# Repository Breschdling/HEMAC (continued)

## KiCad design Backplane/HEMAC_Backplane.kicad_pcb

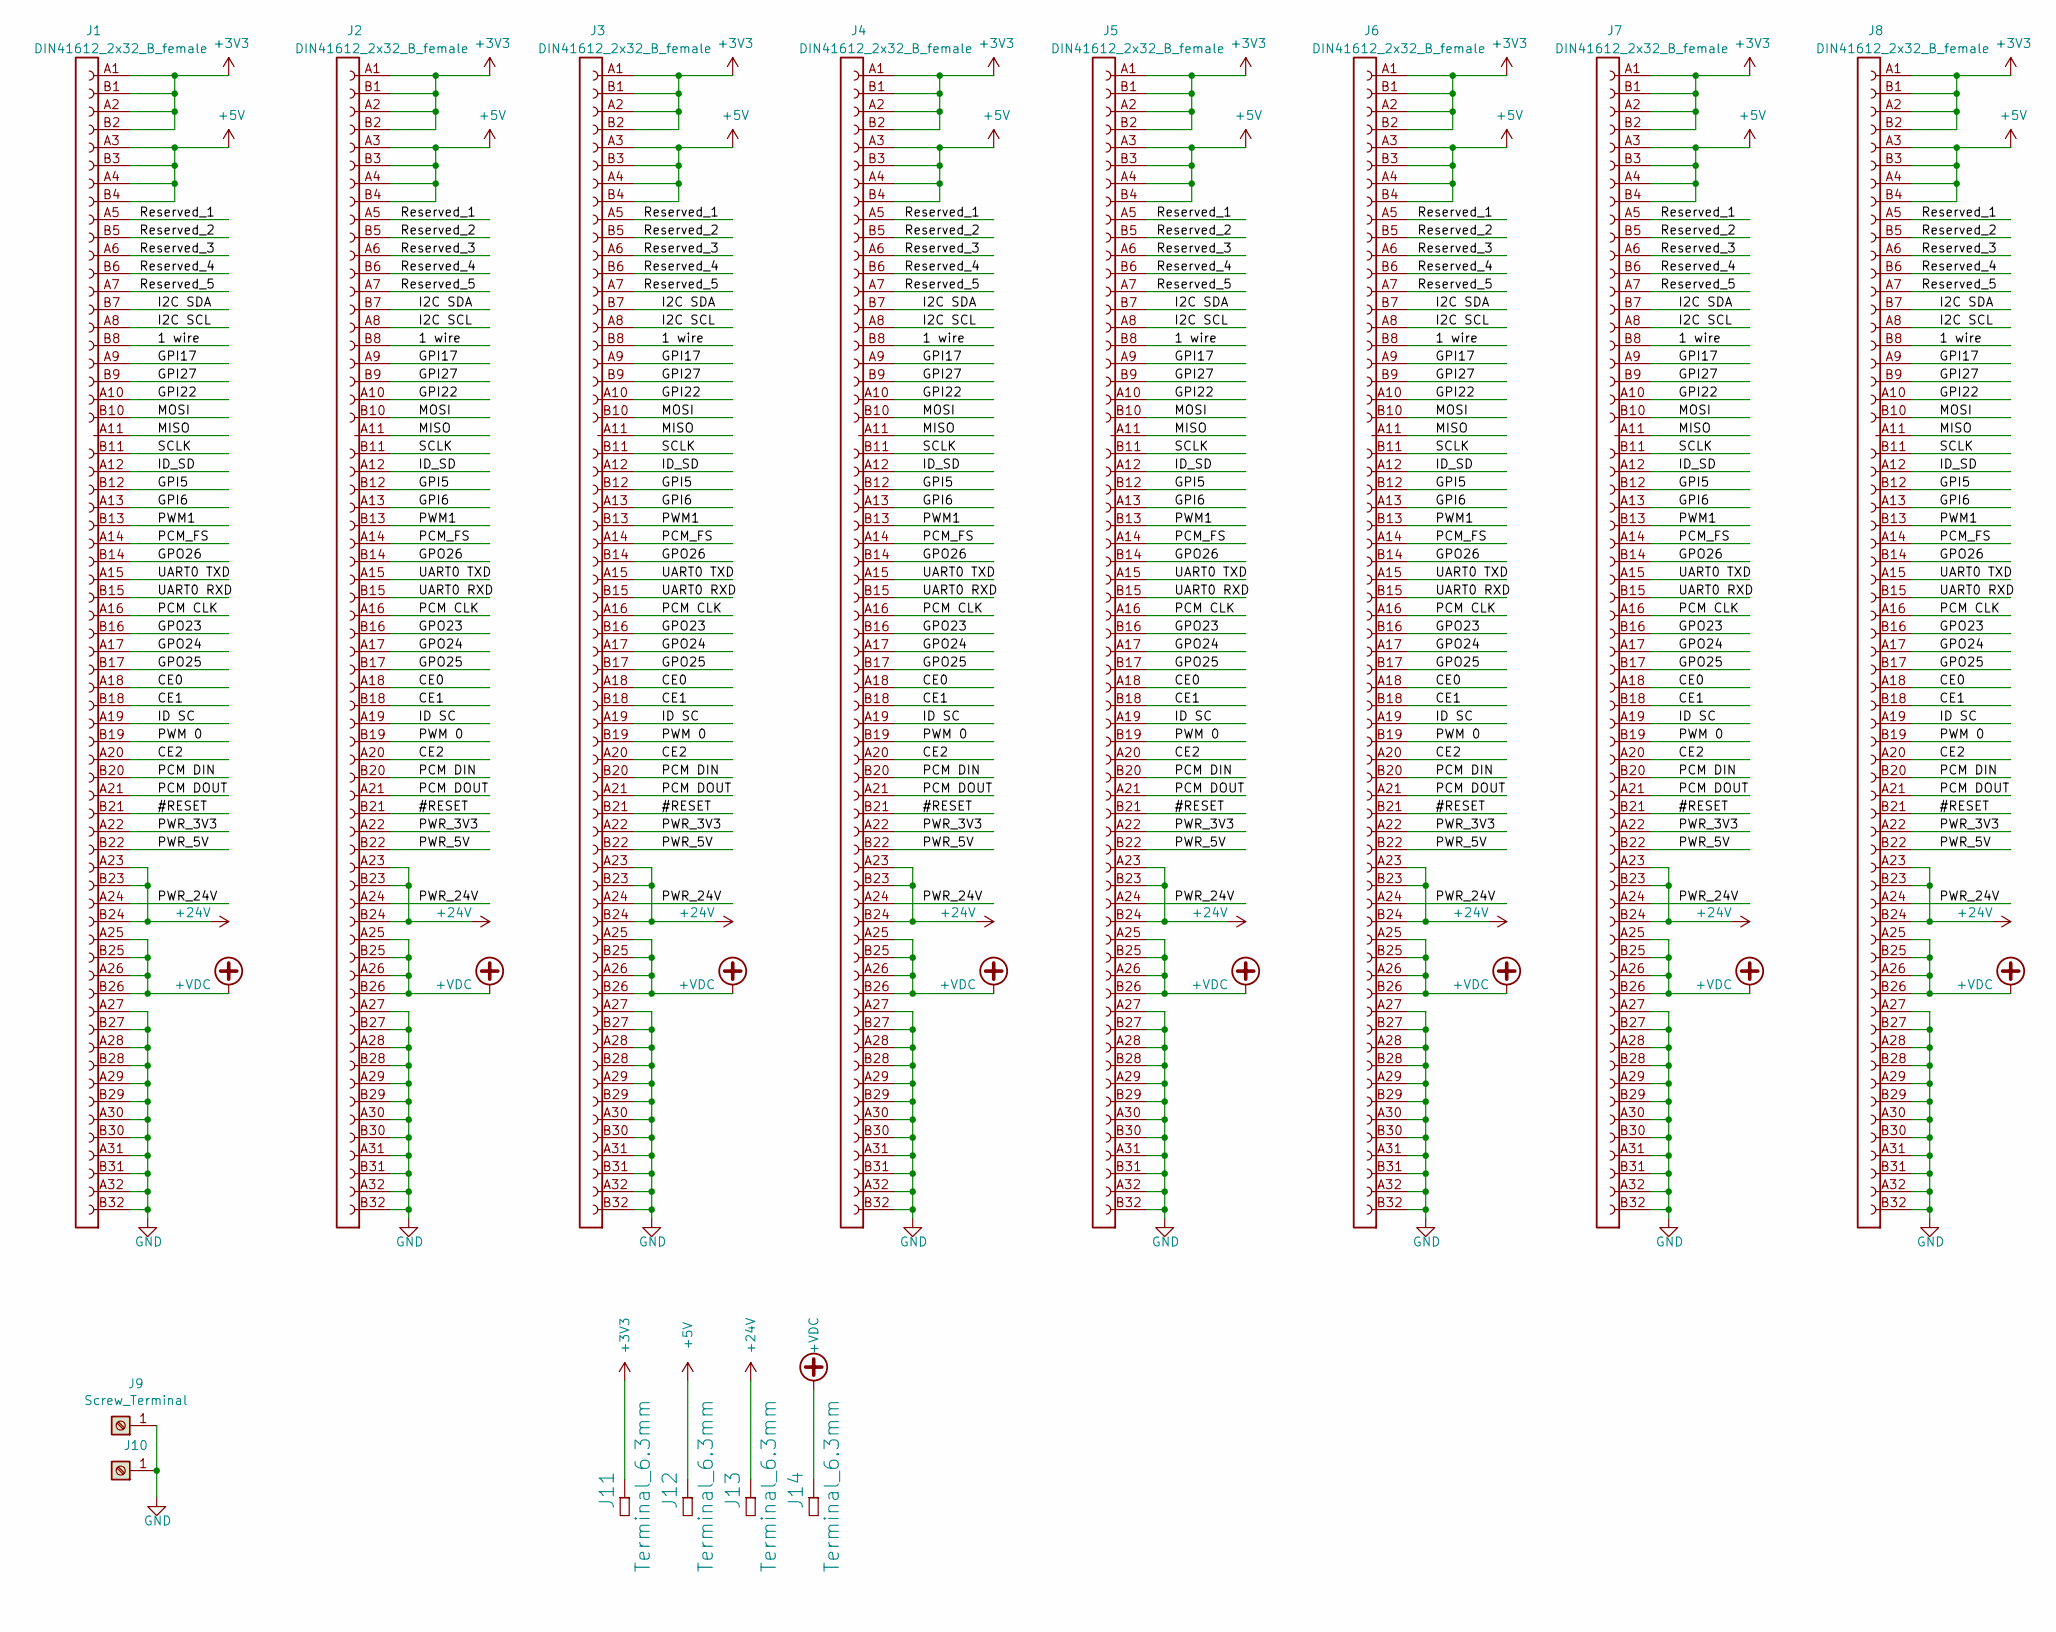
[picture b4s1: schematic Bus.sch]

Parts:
J1, J2, J3, J4, J5, J6, J7, J8: DIN41612_2x32_B_female; DIN41612_B_2x32_Vertical
J9, J10: Screw_Terminal; GD-G13
J11, J12, J13, J14: Terminal_6.3mm; Terminal_6.3mm_THT

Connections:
+3V3: J1.A1 (1A), J1.A2 (2A), J1.B1 (1B), J1.B2 (2B), J2.A1 (1A), J2.A2 (2A), J2.B1 (1B), J2.B2 (2B), J3.A1 (1A), J3.A2 (2A), J3.B1 (1B), J3.B2 (2B), J4.A1 (1A), J4.A2 (2A), J4.B1 (1B), J4.B2 (2B), J5.A1 (1A), J5.A2 (2A), J5.B1 (1B), J5.B2 (2B), J6.A1 (1A), J6.A2 (2A), J6.B1 (1B), J6.B2 (2B), J7.A1 (1A), J7.A2 (2A), J7.B1 (1B), J7.B2 (2B), J8.A1 (1A), J8.A2 (2A), J8.B1 (1B), J8.B2 (2B), J11.1
+5V: J1.A3 (3A), J1.A4 (4A), J1.B3 (3B), J1.B4 (4B), J2.A3 (3A), J2.A4 (4A), J2.B3 (3B), J2.B4 (4B), J3.A3 (3A), J3.A4 (4A), J3.B3 (3B), J3.B4 (4B), J4.A3 (3A), J4.A4 (4A), J4.B3 (3B), J4.B4 (4B), J5.A3 (3A), J5.A4 (4A), J5.B3 (3B), J5.B4 (4B), J6.A3 (3A), J6.A4 (4A), J6.B3 (3B), J6.B4 (4B), J7.A3 (3A), J7.A4 (4A), J7.B3 (3B), J7.B4 (4B), J8.A3 (3A), J8.A4 (4A), J8.B3 (3B), J8.B4 (4B), J12.1
+24V: J1.A23 (23A), J1.B23 (23B), J1.B24 (24B), J2.A23 (23A), J2.B23 (23B), J2.B24 (24B), J3.A23 (23A), J3.B23 (23B), J3.B24 (24B), J4.A23 (23A), J4.B23 (23B), J4.B24 (24B), J5.A23 (23A), J5.B23 (23B), J5.B24 (24B), J6.A23 (23A), J6.B23 (23B), J6.B24 (24B), J7.A23 (23A), J7.B23 (23B), J7.B24 (24B), J8.A23 (23A), J8.B23 (23B), J8.B24 (24B), J13.1
/Bus/1 wire: J1.B8 (8B), J2.B8 (8B), J3.B8 (8B), J4.B8 (8B), J5.B8 (8B), J6.B8 (8B), J7.B8 (8B), J8.B8 (8B)
/Bus/#RESET: J1.B21 (21B), J2.B21 (21B), J3.B21 (21B), J4.B21 (21B), J5.B21 (21B), J6.B21 (21B), J7.B21 (21B), J8.B21 (21B)
/Bus/CE0: J1.A18 (18A), J2.A18 (18A), J3.A18 (18A), J4.A18 (18A), J5.A18 (18A), J6.A18 (18A), J7.A18 (18A), J8.A18 (18A)
/Bus/CE1: J1.B18 (18B), J2.B18 (18B), J3.B18 (18B), J4.B18 (18B), J5.B18 (18B), J6.B18 (18B), J7.B18 (18B), J8.B18 (18B)
/Bus/CE2: J1.A20 (20A), J2.A20 (20A), J3.A20 (20A), J4.A20 (20A), J5.A20 (20A), J6.A20 (20A), J7.A20 (20A), J8.A20 (20A)
/Bus/GPI5: J1.B12 (12B), J2.B12 (12B), J3.B12 (12B), J4.B12 (12B), J5.B12 (12B), J6.B12 (12B), J7.B12 (12B), J8.B12 (12B)
/Bus/GPI6: J1.A13 (13A), J2.A13 (13A), J3.A13 (13A), J4.A13 (13A), J5.A13 (13A), J6.A13 (13A), J7.A13 (13A), J8.A13 (13A)
/Bus/GPI17: J1.A9 (9A), J2.A9 (9A), J3.A9 (9A), J4.A9 (9A), J5.A9 (9A), J6.A9 (9A), J7.A9 (9A), J8.A9 (9A)
/Bus/GPI22: J1.A10 (10A), J2.A10 (10A), J3.A10 (10A), J4.A10 (10A), J5.A10 (10A), J6.A10 (10A), J7.A10 (10A), J8.A10 (10A)
/Bus/GPI27: J1.B9 (9B), J2.B9 (9B), J3.B9 (9B), J4.B9 (9B), J5.B9 (9B), J6.B9 (9B), J7.B9 (9B), J8.B9 (9B)
/Bus/GPO23: J1.B16 (16B), J2.B16 (16B), J3.B16 (16B), J4.B16 (16B), J5.B16 (16B), J6.B16 (16B), J7.B16 (16B), J8.B16 (16B)
/Bus/GPO24: J1.A17 (17A), J2.A17 (17A), J3.A17 (17A), J4.A17 (17A), J5.A17 (17A), J6.A17 (17A), J7.A17 (17A), J8.A17 (17A)
/Bus/GPO25: J1.B17 (17B), J2.B17 (17B), J3.B17 (17B), J4.B17 (17B), J5.B17 (17B), J6.B17 (17B), J7.B17 (17B), J8.B17 (17B)
/Bus/GPO26: J1.B14 (14B), J2.B14 (14B), J3.B14 (14B), J4.B14 (14B), J5.B14 (14B), J6.B14 (14B), J7.B14 (14B), J8.B14 (14B)
/Bus/I2C SCL: J1.A8 (8A), J2.A8 (8A), J3.A8 (8A), J4.A8 (8A), J5.A8 (8A), J6.A8 (8A), J7.A8 (8A), J8.A8 (8A)
/Bus/I2C SDA: J1.B7 (7B), J2.B7 (7B), J3.B7 (7B), J4.B7 (7B), J5.B7 (7B), J6.B7 (7B), J7.B7 (7B), J8.B7 (7B)
/Bus/ID SC: J1.A19 (19A), J2.A19 (19A), J3.A19 (19A), J4.A19 (19A), J5.A19 (19A), J6.A19 (19A), J7.A19 (19A), J8.A19 (19A)
/Bus/ID_SD: J1.A12 (12A), J2.A12 (12A), J3.A12 (12A), J4.A12 (12A), J5.A12 (12A), J6.A12 (12A), J7.A12 (12A), J8.A12 (12A)
/Bus/MISO: J1.A11 (11A), J2.A11 (11A), J3.A11 (11A), J4.A11 (11A), J5.A11 (11A), J6.A11 (11A), J7.A11 (11A), J8.A11 (11A)
/Bus/MOSI: J1.B10 (10B), J2.B10 (10B), J3.B10 (10B), J4.B10 (10B), J5.B10 (10B), J6.B10 (10B), J7.B10 (10B), J8.B10 (10B)
/Bus/PCM CLK: J1.A16 (16A), J2.A16 (16A), J3.A16 (16A), J4.A16 (16A), J5.A16 (16A), J6.A16 (16A), J7.A16 (16A), J8.A16 (16A)
/Bus/PCM DIN: J1.B20 (20B), J2.B20 (20B), J3.B20 (20B), J4.B20 (20B), J5.B20 (20B), J6.B20 (20B), J7.B20 (20B), J8.B20 (20B)
/Bus/PCM DOUT: J1.A21 (21A), J2.A21 (21A), J3.A21 (21A), J4.A21 (21A), J5.A21 (21A), J6.A21 (21A), J7.A21 (21A), J8.A21 (21A)
/Bus/PCM_FS: J1.A14 (14A), J2.A14 (14A), J3.A14 (14A), J4.A14 (14A), J5.A14 (14A), J6.A14 (14A), J7.A14 (14A), J8.A14 (14A)
/Bus/PWM1: J1.B13 (13B), J2.B13 (13B), J3.B13 (13B), J4.B13 (13B), J5.B13 (13B), J6.B13 (13B), J7.B13 (13B), J8.B13 (13B)
/Bus/PWM 0: J1.B19 (19B), J2.B19 (19B), J3.B19 (19B), J4.B19 (19B), J5.B19 (19B), J6.B19 (19B), J7.B19 (19B), J8.B19 (19B)
/Bus/PWR_3V3: J1.A22 (22A), J2.A22 (22A), J3.A22 (22A), J4.A22 (22A), J5.A22 (22A), J6.A22 (22A), J7.A22 (22A), J8.A22 (22A)
/Bus/PWR_5V: J1.B22 (22B), J2.B22 (22B), J3.B22 (22B), J4.B22 (22B), J5.B22 (22B), J6.B22 (22B), J7.B22 (22B), J8.B22 (22B)
/Bus/PWR_24V: J1.A24 (24A), J2.A24 (24A), J3.A24 (24A), J4.A24 (24A), J5.A24 (24A), J6.A24 (24A), J7.A24 (24A), J8.A24 (24A)
/Bus/Reserved_1: J1.A5 (5A), J2.A5 (5A), J3.A5 (5A), J4.A5 (5A), J5.A5 (5A), J6.A5 (5A), J7.A5 (5A), J8.A5 (5A)
/Bus/Reserved_2: J1.B5 (5B), J2.B5 (5B), J3.B5 (5B), J4.B5 (5B), J5.B5 (5B), J6.B5 (5B), J7.B5 (5B), J8.B5 (5B)
/Bus/Reserved_3: J1.A6 (6A), J2.A6 (6A), J3.A6 (6A), J4.A6 (6A), J5.A6 (6A), J6.A6 (6A), J7.A6 (6A), J8.A6 (6A)
/Bus/Reserved_4: J1.B6 (6B), J2.B6 (6B), J3.B6 (6B), J4.B6 (6B), J5.B6 (6B), J6.B6 (6B), J7.B6 (6B), J8.B6 (6B)
/Bus/Reserved_5: J1.A7 (7A), J2.A7 (7A), J3.A7 (7A), J4.A7 (7A), J5.A7 (7A), J6.A7 (7A), J7.A7 (7A), J8.A7 (7A)
/Bus/SCLK: J1.B11 (11B), J2.B11 (11B), J3.B11 (11B), J4.B11 (11B), J5.B11 (11B), J6.B11 (11B), J7.B11 (11B), J8.B11 (11B)
/Bus/UART0 RXD: J1.B15 (15B), J2.B15 (15B), J3.B15 (15B), J4.B15 (15B), J5.B15 (15B), J6.B15 (15B), J7.B15 (15B), J8.B15 (15B)
/Bus/UART0 TXD: J1.A15 (15A), J2.A15 (15A), J3.A15 (15A), J4.A15 (15A), J5.A15 (15A), J6.A15 (15A), J7.A15 (15A), J8.A15 (15A)
GND: J1.A27 (27A), J1.A28 (28A), J1.A29 (29A), J1.A30 (30A), J1.A31 (31A), J1.A32 (32A), J1.B27 (27B), J1.B28 (28B), J1.B29 (29B), J1.B30 (30B), J1.B31 (31B), J1.B32 (32B), J2.A27 (27A), J2.A28 (28A), J2.A29 (29A), J2.A30 (30A), J2.A31 (31A), J2.A32 (32A), J2.B27 (27B), J2.B28 (28B), J2.B29 (29B), J2.B30 (30B), J2.B31 (31B), J2.B32 (32B), J3.A27 (27A), J3.A28 (28A), J3.A29 (29A), J3.A30 (30A), J3.A31 (31A), J3.A32 (32A), J3.B27 (27B), J3.B28 (28B), J3.B29 (29B), J3.B30 (30B), J3.B31 (31B), J3.B32 (32B), J4.A27 (27A), J4.A28 (28A), J4.A29 (29A), J4.A30 (30A), J4.A31 (31A), J4.A32 (32A), J4.B27 (27B), J4.B28 (28B), J4.B29 (29B), J4.B30 (30B), J4.B31 (31B), J4.B32 (32B), J5.A27 (27A), J5.A28 (28A), J5.A29 (29A), J5.A30 (30A), J5.A31 (31A), J5.A32 (32A), J5.B27 (27B), J5.B28 (28B), J5.B29 (29B), J5.B30 (30B), J5.B31 (31B), J5.B32 (32B), J6.A27 (27A), J6.A28 (28A), J6.A29 (29A), J6.A30 (30A), J6.A31 (31A), J6.A32 (32A), J6.B27 (27B), J6.B28 (28B), J6.B29 (29B), J6.B30 (30B), J6.B31 (31B), J6.B32 (32B), J7.A27 (27A), J7.A28 (28A), J7.A29 (29A), J7.A30 (30A), J7.A31 (31A), J7.A32 (32A), J7.B27 (27B), J7.B28 (28B), J7.B29 (29B), J7.B30 (30B), J7.B31 (31B), J7.B32 (32B), J8.A27 (27A), J8.A28 (28A), J8.A29 (29A), J8.A30 (30A), J8.A31 (31A), J8.A32 (32A), J8.B27 (27B), J8.B28 (28B), J8.B29 (29B), J8.B30 (30B), J8.B31 (31B), J8.B32 (32B), J9.1, J10.1
VDC: J1.A25 (25A), J1.A26 (26A), J1.B25 (25B), J1.B26 (26B), J2.A25 (25A), J2.A26 (26A), J2.B25 (25B), J2.B26 (26B), J3.A25 (25A), J3.A26 (26A), J3.B25 (25B), J3.B26 (26B), J4.A25 (25A), J4.A26 (26A), J4.B25 (25B), J4.B26 (26B), J5.A25 (25A), J5.A26 (26A), J5.B25 (25B), J5.B26 (26B), J6.A25 (25A), J6.A26 (26A), J6.B25 (25B), J6.B26 (26B), J7.A25 (25A), J7.A26 (26A), J7.B25 (25B), J7.B26 (26B), J8.A25 (25A), J8.A26 (26A), J8.B25 (25B), J8.B26 (26B), J14.1

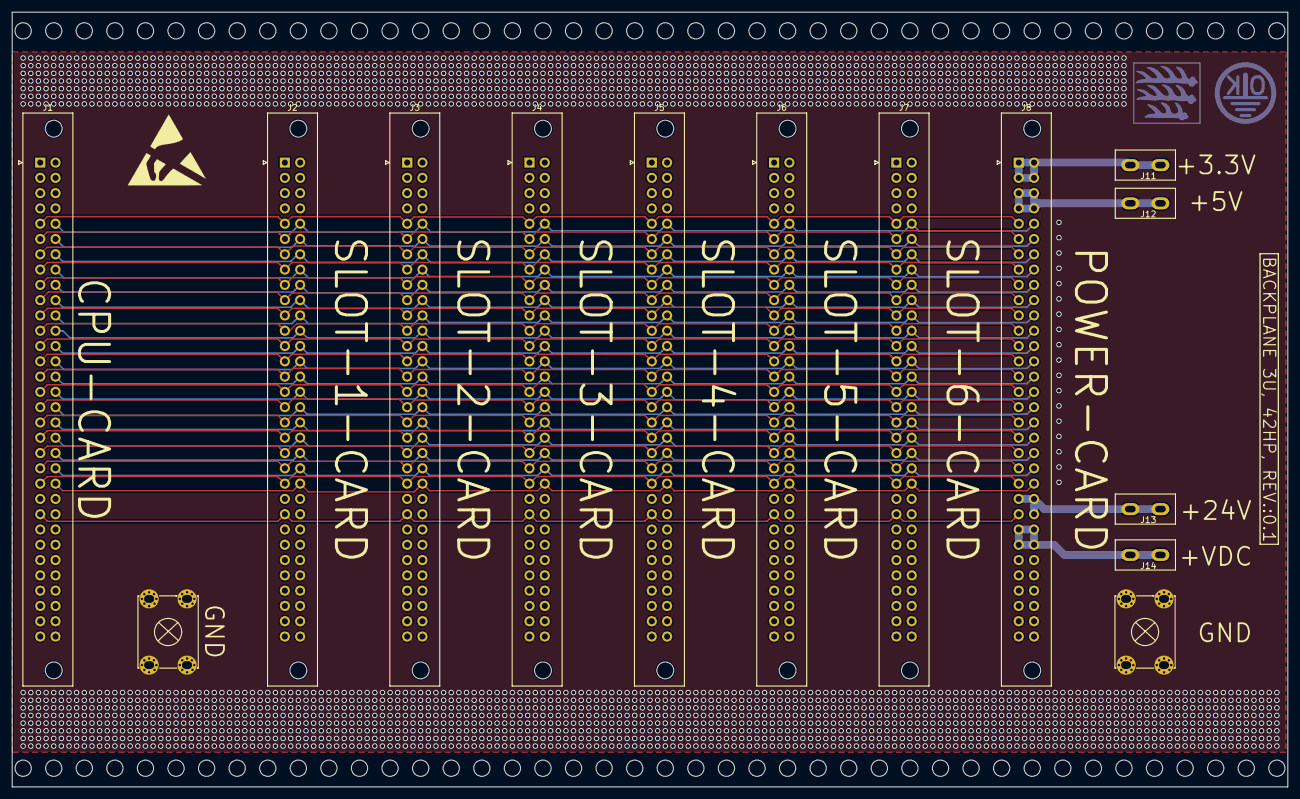
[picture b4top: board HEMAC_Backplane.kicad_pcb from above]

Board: 2 copper layers, 211.9 x 128.7 mm, 14 parts (0 on the bottom side), 42 nets.

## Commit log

2021-03-07 Set theme jekyll-theme-minimal
2021-03-07 Create LICENSE
2023-01-20 Initial upload
